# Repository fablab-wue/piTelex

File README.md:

# - piTelex

## Control a historic Telex device with a Raspberry Pi or PC in Python 3

The goal is to connect a historic telex device (teletype) with **TW39** protocol on a **current loop** to a modern **Windows/Linux-PC** (over USB) or a **Raspberry Pi** (over GPIO) with minimal hardware.

Our ambition is also to support all telex features as AT/ST buttons and pulse dialing for handling the teletype like in the good old days.

For building the hardware and implementing the software it was important to understand the protocols and timings. So, another objective was to pick up the pieces of information a bring it into an understandable form.

### Hardware

One part of the project is the hardware to adapt the **current loop** for **TW39** to modern logic level ports. The 5V or 3.3V TTL lines can be connected directly to an USB-serial-adapter or the GPIO pins of a Raspberry Pi. The current loop is designed as an analog **40mA** current regulator in combination with the switching transistor.

As side effect teletypes with **V.10 interface** (like TeKaDe FS200Z / FS220Z) can also be connected to a USB-to-RS232-adapter with a simple DIY adapter cable. The V.10 interface control lines are completely handled by the software (No FAG200 is needed).

Another playground is the **ED1000 interface** used by (more) modern teletypes (like Siemens T1000, T1200 or SEL Lo2000, Lo3000). It is based on frequency-shift-keying (FSK) and is handled by a USB sound card, a few passive components and a lot of software.

### Software

The other part is the Python software to send and receive the serial data (50 baud, 5 data-bits) and decode the "**Baudot-Murray-Code**" character set (also called "CCITT-2" or "ITA2") to ASCII.

With the characters arrived in the PC / RPi the data can be routed to an internet services like [i-Telex](https://www.i-telex.net), Telnet, eMail, RSS or IRC. The teletype can also be (miss-) used as a steampunk printer or keyboard.

The software supports also a connection to another telex device in the **[i-Telex Network](https://www.i-telex.net)** over TCP/IP.

### Documentation

Comprehensive user documentation concerning installing, configuring and using piTelex can be found under https://github.com/fablab-wue/piTelex/wiki

### Issues, suggestions, questions?

Feel free to share your thoughts at www.telexforum.de. Especially if you cannot get a solution here at github, telexforum is the right place for you! Besides aspects concerning piTelex, the whole world of teletypes, telex and i-telex  is addressed there.

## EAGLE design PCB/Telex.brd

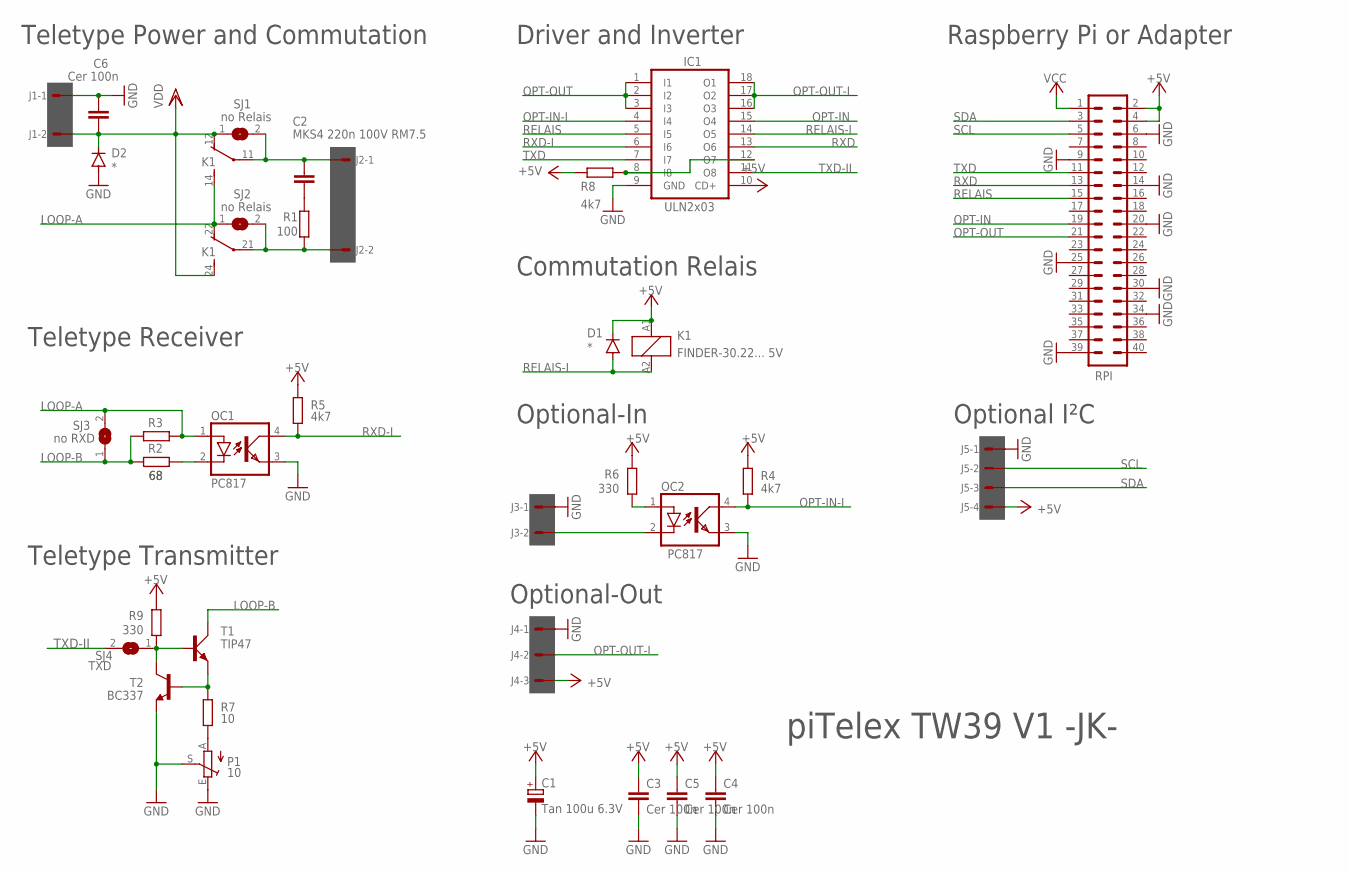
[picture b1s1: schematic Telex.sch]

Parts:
C1: Tan 100u 6.3V; E2,5-6
C2: MKS4 220n 100V RM7.5; C075-042X103
C3, C4, C5, C6: Cer 100n; C050-024X044
D1, D2: *; MINIMELF
IC1: ULN2x03; DIL18
J1, J2, J3: 22-27-2021-02; 6410-02
J4: 22-27-2031-03; 6410-03
J5: 22-27-2041-04; 6410-04
K1: FINDER-30.22... 5V; FINDER-30.22
OC1, OC2: PC817; DIL04
P1: 10; S64Y
R1: 100; 0204/7
R2, R3: 68; 0204/7
R4, R5, R8: 4k7; 0204/7
R6, R9: 330; 0204/7
R7: 10; 0204/7
RPI: MA20-2
SJ1, SJ2: no Relais; SJ
SJ3: no RXD; SJ
SJ4: TXD; SJ
T1: TIP47; TO220AV
T2: BC337; TO92

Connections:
+5V: C1.+, C3.1, C4.1, C5.1, D1.C, IC1.10 (CD+), J4.3, J5.4, K1.A1 (1), R4.1, R5.1, R6.2, R8.1, R9.1, RPI.2, RPI.4
GND: C1.-, C3.2, C4.2, C5.2, C6.2, D2.A, IC1.9 (GND), J1.1, J3.1, J4.1, J5.1, OC1.3 (EMIT), OC2.3 (EMIT), P1.E, P1.S, RPI.6, RPI.9, RPI.14, RPI.20, RPI.25, RPI.30, RPI.34, RPI.39, T2.1 (E)
LOOP-A: K1.14 (S), K1.22 (O), OC1.1 (A), R3.1, SJ2.1, SJ3.2
LOOP-B: R2.2, R3.2, SJ3.1, T1.C
unnamed: C2.2, R1.2
unnamed: OC1.2 (C), R2.1
unnamed: OC2.1 (A), R6.1
unnamed: C2.1, J2.1, K1.11, SJ1.2
unnamed: P1.A, R7.1
unnamed: J2.2, K1.21, R1.1, SJ2.2
unnamed: J3.2, OC2.2 (C)
unnamed: R7.2, T1.E, T2.2 (B)
OPT-IN: IC1.15 (O4), RPI.19
OPT-IN-I: IC1.4 (I4), OC2.4 (COL), R4.2
OPT-OUT: IC1.1 (I1), IC1.2 (I2), IC1.3 (I3), RPI.21
OPT-OUT-I: IC1.16 (O3), IC1.17 (O2), IC1.18 (O1), J4.2
RELAIS: IC1.5 (I5), RPI.15
RELAIS-I: D1.A, IC1.14 (O5), K1.A2 (2)
RXD: IC1.13 (O6), RPI.13
RXD-I: IC1.6 (I6), OC1.4 (COL), R5.2
SCL: J5.2, RPI.5
SDA: J5.3, RPI.3
TXD: IC1.7 (I7), RPI.11
TXD-II: IC1.11 (O8), SJ4.2
TXD-IIX: R9.2, SJ4.1, T1.B, T2.3 (C)
TXT-I: IC1.8 (I8), IC1.12 (O7), R8.2
VCC: RPI.1
VDD: C6.1, D2.C, J1.2, K1.12 (O), K1.24 (S), SJ1.1

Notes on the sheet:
piTelex TW39 V1 -JK-
Optional-Out
Optional-In
Commutation Relais
Driver and Inverter
Raspberry Pi or Adapter
Teletype Power and Commutation
Teletype Receiver
Teletype Transmitter
Optional I²C

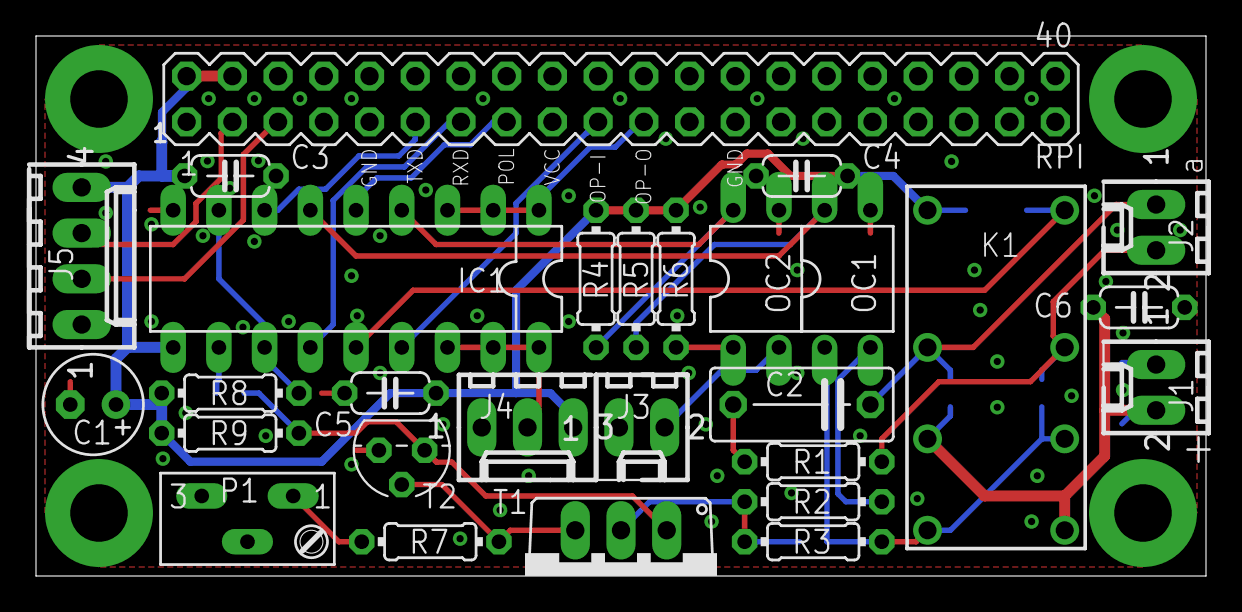
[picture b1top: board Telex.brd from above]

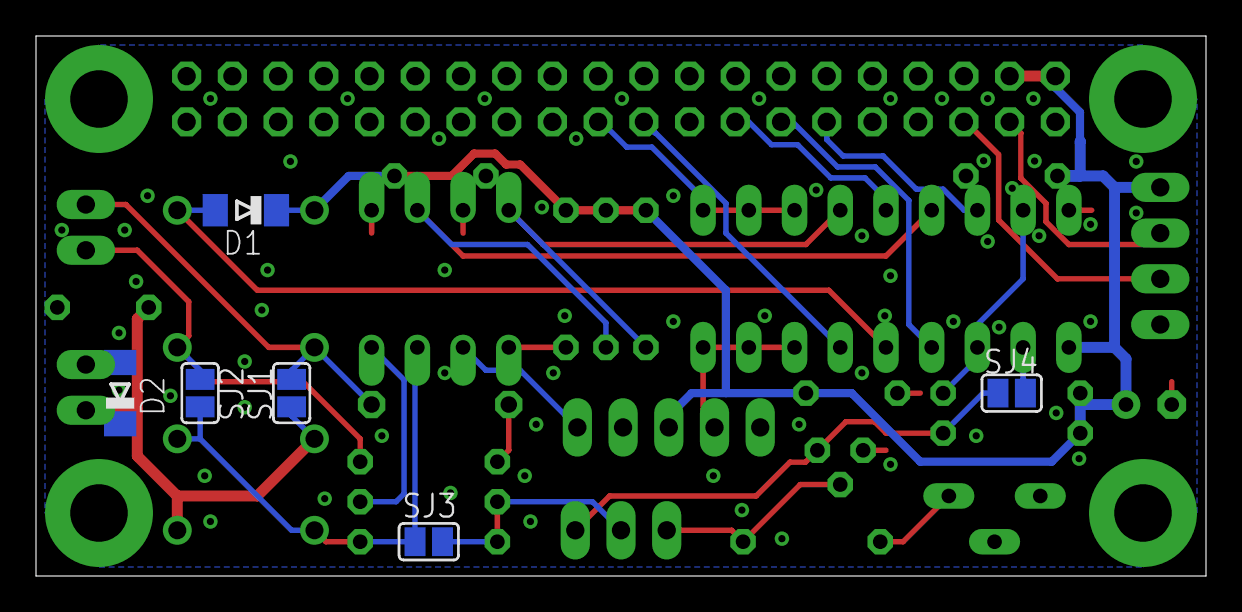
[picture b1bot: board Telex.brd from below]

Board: 2 copper layers, 65.0 x 30.0 mm, 34 parts (6 on the bottom side), 27 nets.

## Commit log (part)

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2020-08-30 added device Terminal
2020-09-03 optimized printing FIFO info
2020-09-03 added printer FIFO info for RPiTTY
2020-09-17 added ESC-A to 'nc'
2020-09-22 rework of RPiTTY TW39
2020-09-26 i-Telex Acknowledge throttling
    Special problems manifested themselves in conjunction with the circular
    service 11150, when calling piTelex as recipient of circulars:
    1. Previously, piTelex gobbled up all data sent via i-Telex as fast as it
    could, and fed it to the teleprinter driver module, which manages the
    printing process. All read characters were instantly reported as
    "printed" in Acknowledge packets, which lead remotes to believe they
2020-09-27 added source to ESC infos
2020-09-27 global renaming of module IDs
2020-10-23 rework and V.10 features
2020-10-24 Rename i-Telex module option "number"
    To avoid confusion, rename configuration option "number" to
    "tns-dynip-number".
    Prevent breaking users' configurations by accepting the old option, but
    also log a warning.
2020-10-24 txDevITelexCommon: Improve Acknowledge counter calculation
    The i-Telex Acknowledge counter communicates how many characters already
    have been committed to paper. It's calculated as the number of received
    characters minus the current printer buffer length.
    What had previously been overlooked however is that freshly received characters
    aren't instantaneously committed to the printer buffer, but linger for a
    short time inside txDevITelexCommon's _rx_buffer -- a purgatory as it
2020-10-25 txDevMCP: Emergency fix for Acknowledge
    In the previous rework, the sending of the ESC-WELCOME command was
    modified. This caused piTelex as server to not send any i-Telex
    Acknowledge packets. Fix by reintroducing leading ESC.
2020-10-26 allow alphanumeric dialing for shortlist
2020-10-27 telex.py: Also print exceptions to console
    Previously, exceptions were only committed to the error log. To ease
    recognition of errors, print exceptions also to console.
2020-10-28 txDevMCP: On entering S_SLEEPING, reset ACTIVE wd
    Previously, when going offline, the ACTIVE watchdog was disabled. If
    there had been any data left in the teleprinter buffer, subsequent
    receipt of an ESC-~ command would re-enable the ACTIVE wd again,
    inadvertently advancing state to S_OFFLINE and thus turning teleprinter
    power on again.
    Fix this by only triggering said watchdog when still online.
2020-10-29 txDevED1000SC: Report/send AT in offline only once
    ... to prevent the "AT storm" resulting from a delay to go online.
2020-10-30 work release for state rework
2020-10-30 txDevMCP: Fix if/iteration bug leading to immediate power-off
    There were if statements iterating over tuples, which had been changed
    to seemingly single-element tuples. Because the trailing comma was
    missing, the string inside was iterated over, leading to wrong matches.
    Specifically:
    if a in ("Z", "ZZ"):
    do thing
2020-11-06 added keep alive counter for V.10 printers
2020-11-07 Move find_rev to telex.py, clarify error msg, suppress stderr
    Previously, find_rev was resident in txDevLog.py, but also used in
    telex.py. This lead to confusion since txDevLog code was used even
    though txDevLog was disabled in the configuration.
    So move find_rev to telex.py and import in txDevLog.
    Also, clarify error displayed on piTelex start (in error log) in case
    the current git HEAD revision cannot be found.
2020-11-22 Add files via upload
    Tried to set up an overall list of parameters for use in telex.json. Reviewed partially by Björn, but there is still some need for correction/completion, especially in the 'comment' field.
2020-11-28 added documentation to paramlist
2020-12-31 txDevMCP: Prevent double dialling
    It was possible to create two i-Telex client connections when using
    timed dialling: Just press + before the timeout runs out.
    Prevent this by allowing plus dialling only when explicitly configured.
    To these ends, employ a non-magic, clearly recognisable sentinel value
    for self._dial_timeout. Python's sys.maxsize seems ok (on GNU/Linux,
    currently seems to be the maximum value for a signed 64-bit integer).
2021-01-10 minor formatting updates
2021-02-20 Add commentjson requirement and warning
    As the default telex.json contains comments non-compliant with JSON
    standard, add commentjson module as requirement, and output a warning if
    it cannot be found during startup. (Previously, we would fall back
    silently to the normal json module, and output a mildly confusing
    configuration file error.)
2021-02-28 Add LED pin for local mode
2022-01-09 txDevITelex*: After disconnect, pause until tp buffer empty
    Correct acknowledge counter calculation is vital for proper buffer
    management by the remote peer. As it is calculated from the received
    bytes in this connection minus all intermediate buffer contents, it is
    important that a connection starts with empty buffers.
    During normal operation, this was mostly being achieved, the frequent
    exception being multiple consecutive connections by automated services.
2022-01-09 txDevITelexCommon: Remove unused references
2022-01-09 txDevArchive: Ignore rogue ESC-WB commands
    The archive module starts recording after ESC-A command and saves the
    message at ESC-Z. The ESC-WB command is used to determine the outgoing
    number (used for naming the respective archive file).
    The typical sequences are:
    1. ESC-A, message, ESC-Z (incoming)
    2. ESC-WB, dialling, ESC-A, message, ESC-Z (outgoing)
2022-01-09 Add .pylintrc
    To ease debugging, add a tailored pylintrc.
    It was created using --generate-rcfile with:
    pylint 2.11.1
    astroid 2.8.5
    Python 3.7.3 (default, Jan 22 2021, 20:04:44)
    [GCC 8.3.0]
2022-01-16 txDevITelexSrv.py: Tighten own Telex number check
    i-Telex numbers must not only fit into a 32-bit integer, but must also
    be at least five digits long (no leading noughts). Tighten the check
    accordingly.
2022-01-18 txDevED1000SC: Change condition for sending printer buffer feedback
    Printer buffer feedback triggers recalculation of the Acknowledge
    counter in the i-Telex module, which is important for the sender to know
    how much of the sent data we've printed yet.
    Up until now, ESC-~ was sent only if the current buffer length changed.
    When transmitting "full throttle" this is no problem, but when
    transmitting only single characters this may cause the connection to
2022-03-19 txDevRPiTTY.py: Ensure sending ESC-~0 on shutdown
    txDevITelex* needs to know the buffer is empty to completely reset its
    state (and thus make us reachable again via i-Telex), so it is
    imperative that the hardware's last buffer feedback be 0 (empty).
    Ensure this by recalculating the buffer independently from our state, so
    that even after receipt of ESC-Z, while the rest of the buffer contents
    (if present) are being printed, buffer feedback (ESC-~) will be sent
2022-04-14 ED1000/asoundrc-for-recording: Add ALSA config for ED1000 snooping
    For debugging purposes, it's often helpful to record both A=>B and B=>A
    channels of ED1000. This template can be used for ~/.asoundrc to create
    an ALSA device to these ends.
2022-07-10 txDevArchive.py: Critical: Remove bad chars in filename
    The Archive module's filename method didn't check the wru argument for
    bad characters. If there was a "/" inside the wru, it would carry over
    to the filename. On all supported platforms however slashes are
    forbidden.
    Also, catch exceptions whilst writing the file. In one occasion, the
    above happened (slash inside filename) and a FileNotFoundError was
2022-07-22 need to try/catch here
2022-08-06 txDevRPiCtrl: Add GPIO output for local mode LED
    As local mode has no distinct state, a flag is needed.
    Thanks to Rolf for this patch.
    Functional sequence:
    - When the LT button is pressed, ESC-LT is sent to MCP (as usual) and a
    flag is set.
    - As soon as MCP's ESC-A arrives in return, the flag having been set
2022-08-06 txDevMCP: Make power timers configurable
    There is a power timer which has two hard-coded timeouts. Make them
    configurable (both in s).
    - power_off_delay: The power off delay after a connection is terminated
    (default 20 s)
    - power_button_timeout: The power off delay after power has been turned
    on using the power toggle button (ESC-PT) (default 5 min)
2022-08-10 Make sure that the @ sign is translated Fixes issue #21
2022-08-14 txDevMCP: Change PT logic
    There are two times concerning power-off:
    - power_off_delay: The power off delay after a connection is terminated
    (default 20 s)
    - power_button_timeout: The power off delay after power has been turned
    on using the power toggle button (ESC-PT) (default 5 min)
    Before this change, if you used the PT, the (normally longer)
2022-08-15 Added a downstripped version of telex.json
    The full blown example of telex.json may be confusing for beginners. This stripped down version concentrates on Teletype entries, i-Telex entries and some debugging/logging facilities. Furthermore, s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
2022-08-16 Cleanup: Delete deprecated directive "pin_fsg_ns"
    "pin_fsg_ns" had been replaced by "pin_number_switch" and "inv_number_switch" earlier
2022-08-18 Update Userlevel-Changes.md
    Correct some typos
2022-08-31 replace tns-dynip-number and tns-pin by undersore varaints
    To harmonize the syntax of the config file parameters, replace
    - "tns-dynip-number" by "tns_dynip_number" and
    - "tns-pin" by "tns_pin".
    The old variants are still accepted but throw a warning message
2022-09-06 Add config file parameter "errorlog_level"
    Error log was fixed to INFO level by default and could only be changed by editing the main file telex.py.
    Introducing the cfg file param "errlog_level" in the global section now allows for better control; available levels are NOTSET, DEBUG, INFO, WARN, ERROR, CRITICAL.
    default level is still INFO, which is also set if an unknown or mistyped entry is found.
2022-09-15 Minor fixes
    txDevRPiCtrl.py : Correct typo: wrong delay param delay_AT was used for ST function;
    txDevNews.py: Added ESC-ST at EOM: switch printer off immediately after message has been printed (don't wait for 'A' timeout)
2022-11-01 correct news path
2022-12-04 TNS addresses updated
    according to Fred's change announcement in https://telexforum.de/viewtopic.php?p=34877#p34877
2022-12-30 comments in telex.json
2023-01-06 fixed startup condition of power pin and number switch
2023-01-06 Solved merge conflicts from Rolf-branch
2023-01-10 work around for ESC~0
    + refactoring
2023-02-02 cleanup the configuration file acc. to Rolf
2023-02-16 added new module: KeyPad USB-KeyPad input for text shortcuts and test teletypes
2023-02-24 deleted
2023-02-27 introduce pin_button_wakeup
    rename option "pin_wakeup" to "pin_button_wakeup" for unification reasons
2023-03-12 added more description
2023-03-12 fixed 'import log'
2023-04-11 correct typo and pathnames
2023-04-20 added hand type simulator
2023-07-27 Update telex.json
    Use current directory for paths and files to avoid errmsgs complaining about "path/file not found".
2023-08-03 new small tool
2023-10-11 Update UserlevelChanges.md
    Error correction
2023-10-24 Feature: switch off current loop when in power save mode; exit routine
2023-10-27 Delete utils/mail-notify/notify-new-telex.sh
    replaced by txnotify.sh
2023-12-28 Reverting back to original
2023-12-28 Adding a linefeed at the bottom again
2023-12-28 Added requirements.txt and updated readme.md
2024-01-03 Need this as wel to protect private.json
2024-02-02 stop loop current in 'ZZ'/move pwr relay > RPiCtrl
2024-02-04 Ignore 'ZI' before filename
2024-02-26 Adding a ChatGPT socket client
2024-08-08 Only send ESC-Z after an *accepted* and not blocked/ignored incoming connection
2025-01-21 Show release information in i-Telex version packet
2025-01-23 Version tests
2025-01-23 Version info
2025-01-24 Log remote version string
2025-01-25 Additional logging
2025-01-28 log centralex errror response 0xff
2025-02-10 Update txDevNews.py: cleanup
    remove unused print_path option
2025-02-18 bugfix
    modified formatting of the output
2025-02-26 corrected typo
2025-04-05 Update txDevArchive.py
    Mail notification: delete invalid chars instead of replacing them with an underscore. This optimizes the readability of the output without loss of information.
2025-06-17 Update txReleaseInfo.py
    Update release code
2025-08-17 verbesserte Version
    Prompt geändert und Texterkennung
    Kennungsdetektor raus...
2025-11-03 Fixed: some i-telex connection closed exceptions was causing stopping the i-telex-server.
2025-11-05 Resolve release date conflict and update date
2025-11-21 Update UserlevelChanges with new CLI commands
    Added new CLI commands for WLAN and IP information.
2025-12-22 Update release_number to '003'
2025-12-29 Update SW_StartMsg.md with backend diagnostics note
    Added a note about missing backend diagnostics.
2026-01-30 Add time squelch setting for motor activation
    Set time squelch to 0.5 seconds before motor starts.
2026-05-14 Minor: telex.py,Archive,Babelfish,CH340,ED1000,RPiTTY; Major: CLI,StartMsg; new: Answerbox
